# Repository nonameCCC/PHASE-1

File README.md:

# PHASE-1
A compact modularized audio DAC &amp; Headphone Amplifier.

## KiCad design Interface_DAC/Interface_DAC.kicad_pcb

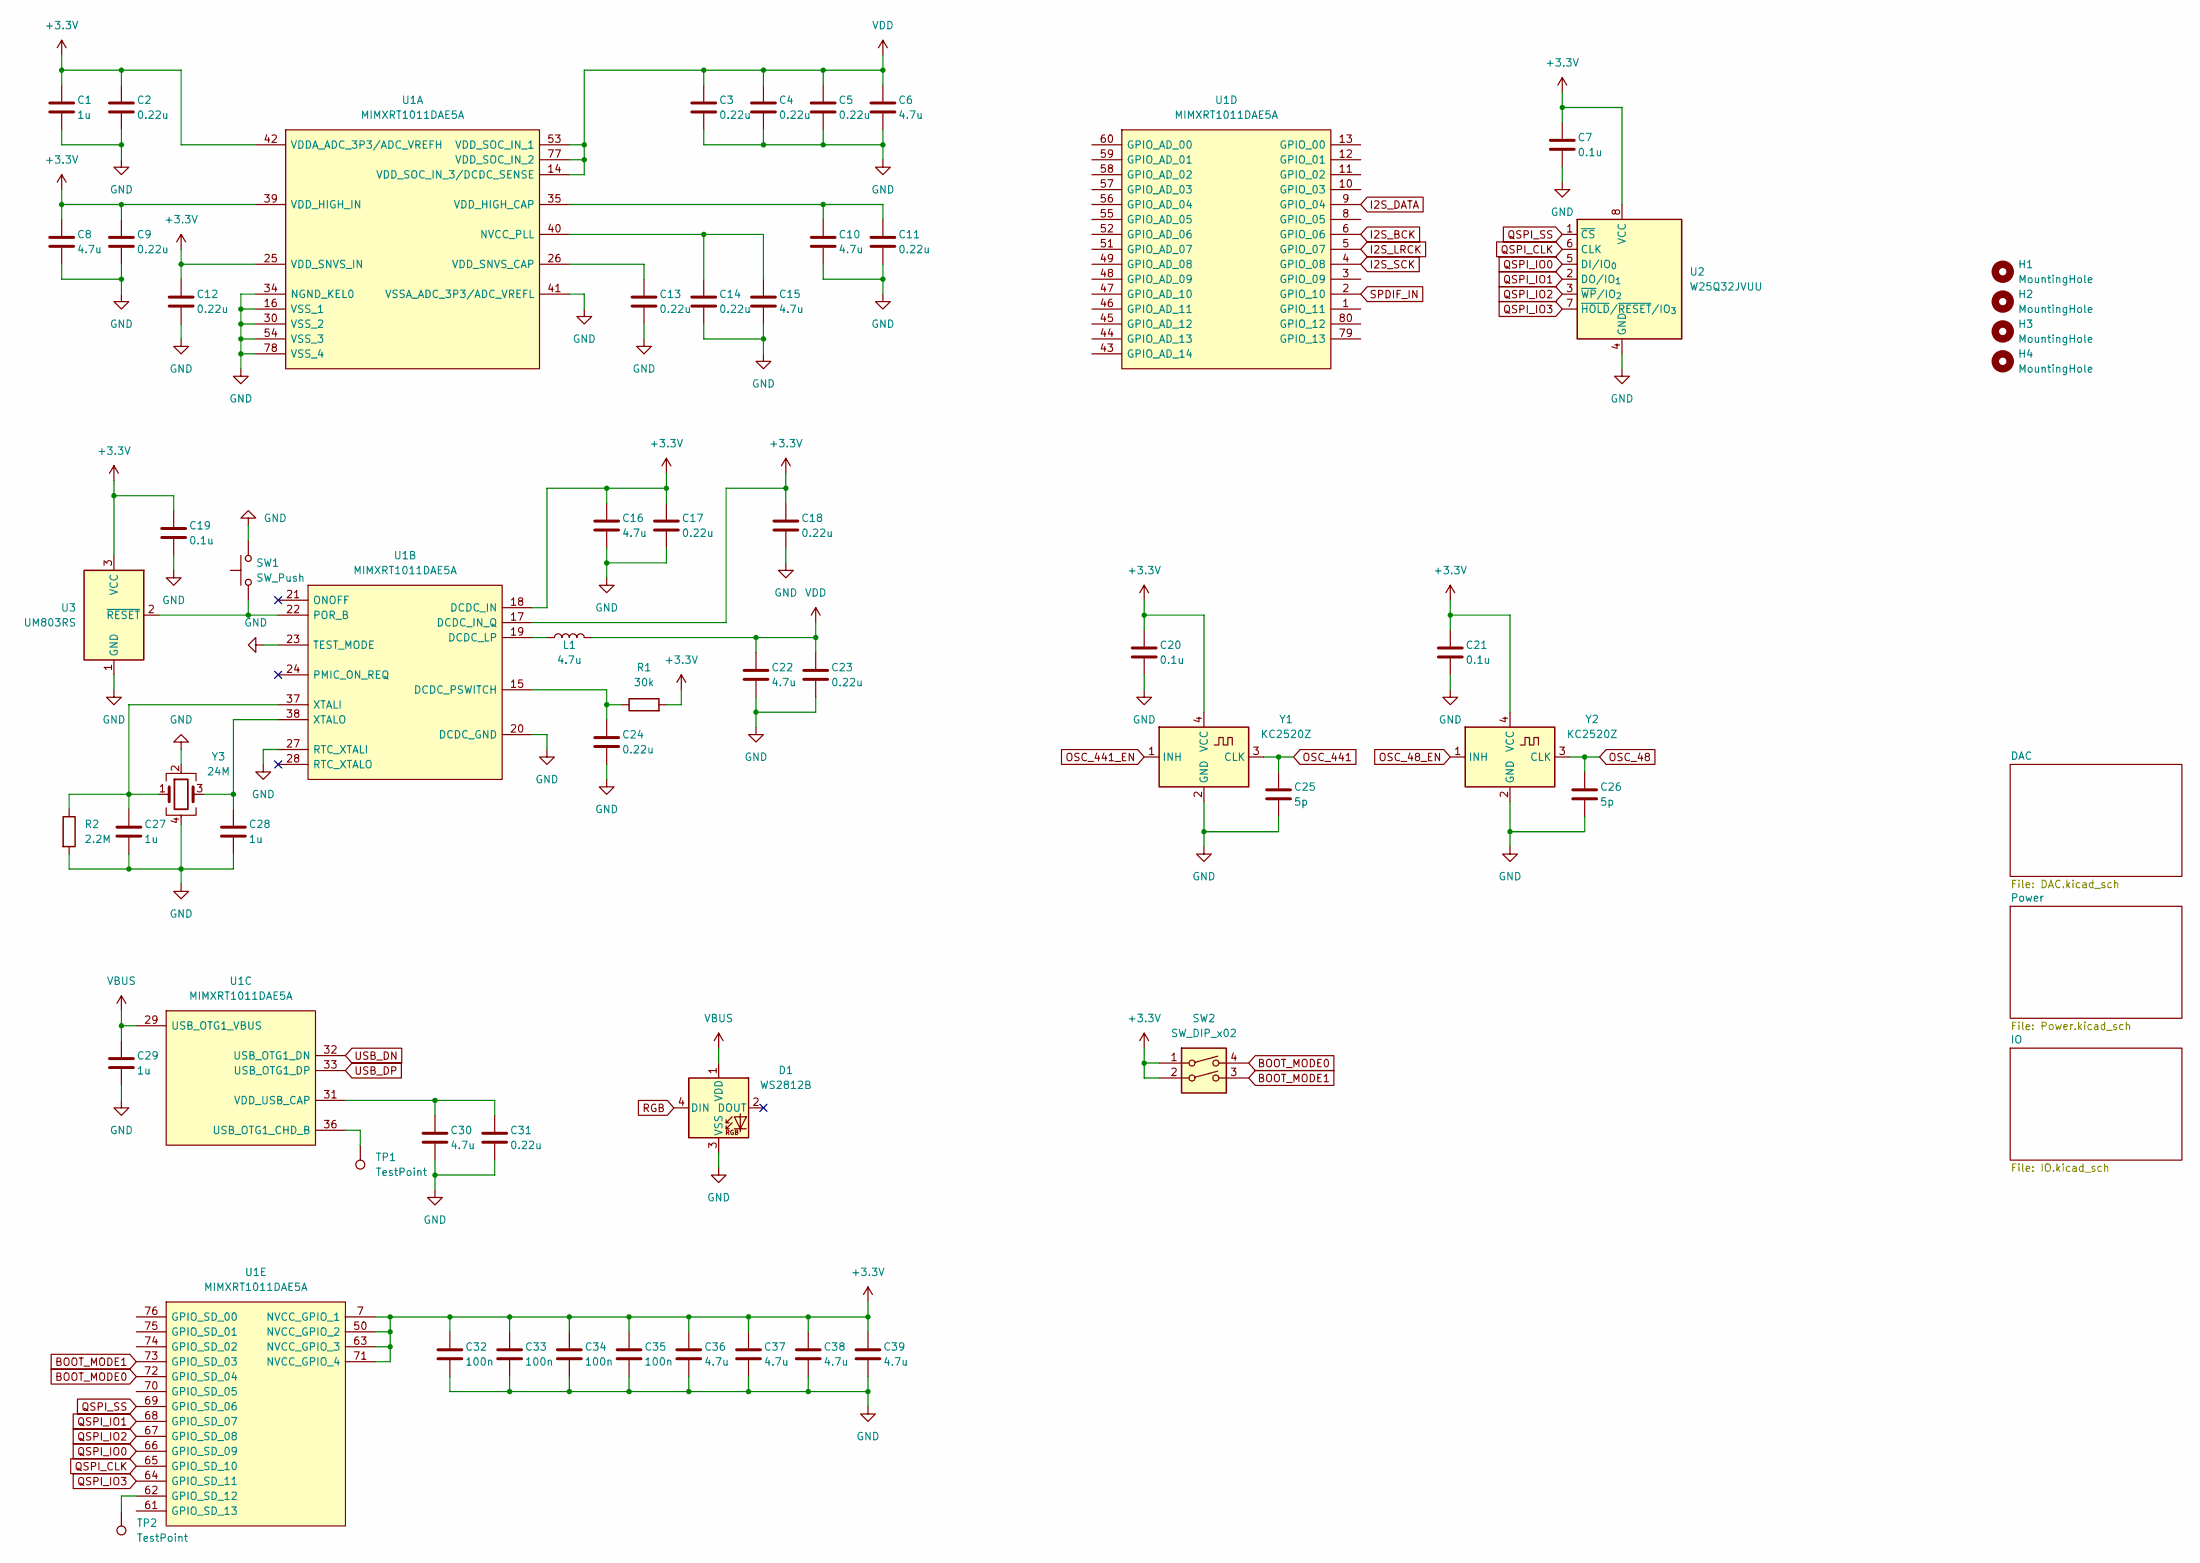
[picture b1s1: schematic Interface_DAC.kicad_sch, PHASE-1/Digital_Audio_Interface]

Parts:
C1, C27, C28, C29: 1u; C_0402_1005Metric
C2, C3, C4, C5, C9, C11, C12, C13, C14, C17, C18, C23, C24, C31: 0.22u; C_0402_1005Metric
C6, C8, C10, C15, C16, C22, C30, C36, C37, C38, C39: 4.7u; C_0402_1005Metric
C7, C19, C20, C21: 0.1u; C_0402_1005Metric
C25, C26: 5p; C_0402_1005Metric
C32, C33, C34, C35: 100n; C_0402_1005Metric
D1: WS2812B; 4020_WS2812
H1, H2, H3, H4: MountingHole; MountingHole_2.2mm_M2
L1: 4.7u; L_Murata_DFE201610P
R1: 30k; R_0402_1005Metric
R2: 2.2M; R_0402_1005Metric
SW1: SW_Push; PinHeader_1x02_P1.27mm_Vertical
SW2: SW_DIP_x02; SW_DIP_SPSTx02_Slide_Copal_CHS-02B_W7.62mm_P1.27mm
TP1, TP2: TestPoint; TestPoint_Pad_D1.0mm
U1: MIMXRT1011DAE5A; LQFP-80_12x12mm_P0.5mm; Manufacturer_Part_Number MIMXRT1011DAE5A; Mouser Part Number 771-MIMXRT1011DAE5A
U2: W25Q32JVUU; Winbond_USON-8-2EP_3x4mm_P0.8mm_EP0.2x0.8mm
U3: UM803RS; SOT-23
Y1, Y2: KC2520Z; Oscillator_SMD_Kyocera_KC2520Z-4Pin_2.5x2.0mm
Y3: 24M; Oscillator_SMD_Kyocera_KC2520Z-4Pin_2.5x2.0mm

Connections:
+3.3V: C1.1, C2.1, C7.1, C8.1, C9.1, C12.1, C16.1, C17.1, C18.1, C19.1, C20.1, C21.1, C32.1, C33.1, C34.1, C35.1, C36.1, C37.1, C38.1, C39.1, R1.2, SW2.1, SW2.2, U1.7 (NVCC_GPIO_1), U1.17 (DCDC_IN_Q), U1.18 (DCDC_IN), U1.25 (VDD_SNVS_IN), U1.39 (VDD_HIGH_IN), U1.42 (VDDA_ADC_3P3/ADC_VREFH), U1.50 (NVCC_GPIO_2), U1.63 (NVCC_GPIO_3), U1.71 (NVCC_GPIO_4), U2.8 (VCC), U3.3 (VCC), Y1.4 (VCC), Y2.4 (VCC); also elsewhere on the board
BOOT_MODE0: SW2.4, U1.72 (GPIO_SD_04)
BOOT_MODE1: SW2.3, U1.73 (GPIO_SD_03)
GND: C1.2, C2.2, C3.2, C4.2, C5.2, C6.2, C7.2, C8.2, C9.2, C10.2, C11.2, C12.2, C13.2, C14.2, C15.2, C16.2, C17.2, C18.2, C19.2, C20.2, C21.2, C22.2, C23.2, C24.2, C25.2, C26.2, C27.2, C28.2, C29.2, C30.2, C31.2, C32.2, C33.2, C34.2, C35.2, C36.2, C37.2, C38.2, C39.2, D1.3 (VSS), R2.2, SW1.2, U1.16 (VSS_1), U1.20 (DCDC_GND), U1.23 (TEST_MODE), U1.27 (RTC_XTALI), U1.30 (VSS_2), U1.34 (NGND_KEL0), U1.41 (VSSA_ADC_3P3/ADC_VREFL), U1.54 (VSS_3), U1.78 (VSS_4), U2.4 (GND), U3.1 (GND), Y1.2 (GND), Y2.2 (GND), Y3.2, Y3.4; also elsewhere on the board
I2S_BCK: U1.6 (GPIO_06); also elsewhere on the board
I2S_DATA: U1.9 (GPIO_04); also elsewhere on the board
I2S_LRCK: U1.5 (GPIO_07); also elsewhere on the board
I2S_SCK: U1.4 (GPIO_08); also elsewhere on the board
unnamed: C14.1, C15.1, U1.40 (NVCC_PLL)
unnamed: C10.1, C11.1, U1.35 (VDD_HIGH_CAP)
unnamed: C13.1, U1.26 (VDD_SNVS_CAP)
unnamed: L1.1, U1.19 (DCDC_LP)
unnamed: C24.1, R1.1, U1.15 (DCDC_PSWITCH)
unnamed: SW1.1, U1.22 (POR_B), U3.2 (~RESET)
unnamed: C27.1, R2.1, U1.37 (XTALI), Y3.1
unnamed: C28.1, U1.38 (XTALO), Y3.3
unnamed: TP1.1, U1.36 (USB_OTG1_CHD_B)
unnamed: C30.1, C31.1, U1.31 (VDD_USB_CAP)
unnamed: TP2.1, U1.62 (GPIO_SD_12)
OSC_48: C26.1, Y2.3 (CLK)
OSC_48_EN: Y2.1 (INH)
OSC_441: C25.1, Y1.3 (CLK)
OSC_441_EN: Y1.1 (INH)
QSPI_CLK: U1.65 (GPIO_SD_10), U2.6 (CLK)
QSPI_IO0: U1.66 (GPIO_SD_09), U2.5 (DI/IO_{0})
QSPI_IO1: U1.68 (GPIO_SD_07), U2.2 (DO/IO_{1})
QSPI_IO2: U1.67 (GPIO_SD_08), U2.3 (~WP/IO_{2})
QSPI_IO3: U1.64 (GPIO_SD_11), U2.7 (~HOLD/~RESET/IO_{3})
QSPI_SS: U1.69 (GPIO_SD_06), U2.1 (~CS)
RGB: D1.4 (DIN)
SPDIF_IN: U1.2 (GPIO_10)
USB_DN: U1.32 (USB_OTG1_DN); also elsewhere on the board
USB_DP: U1.33 (USB_OTG1_DP); also elsewhere on the board
VBUS: C29.1, D1.1 (VDD), U1.29 (USB_OTG1_VBUS); also elsewhere on the board
VDD: C3.1, C4.1, C5.1, C6.1, C22.1, C23.1, L1.2, U1.14 (VDD_SOC_IN_3/DCDC_SENSE), U1.53 (VDD_SOC_IN_1), U1.77 (VDD_SOC_IN_2)

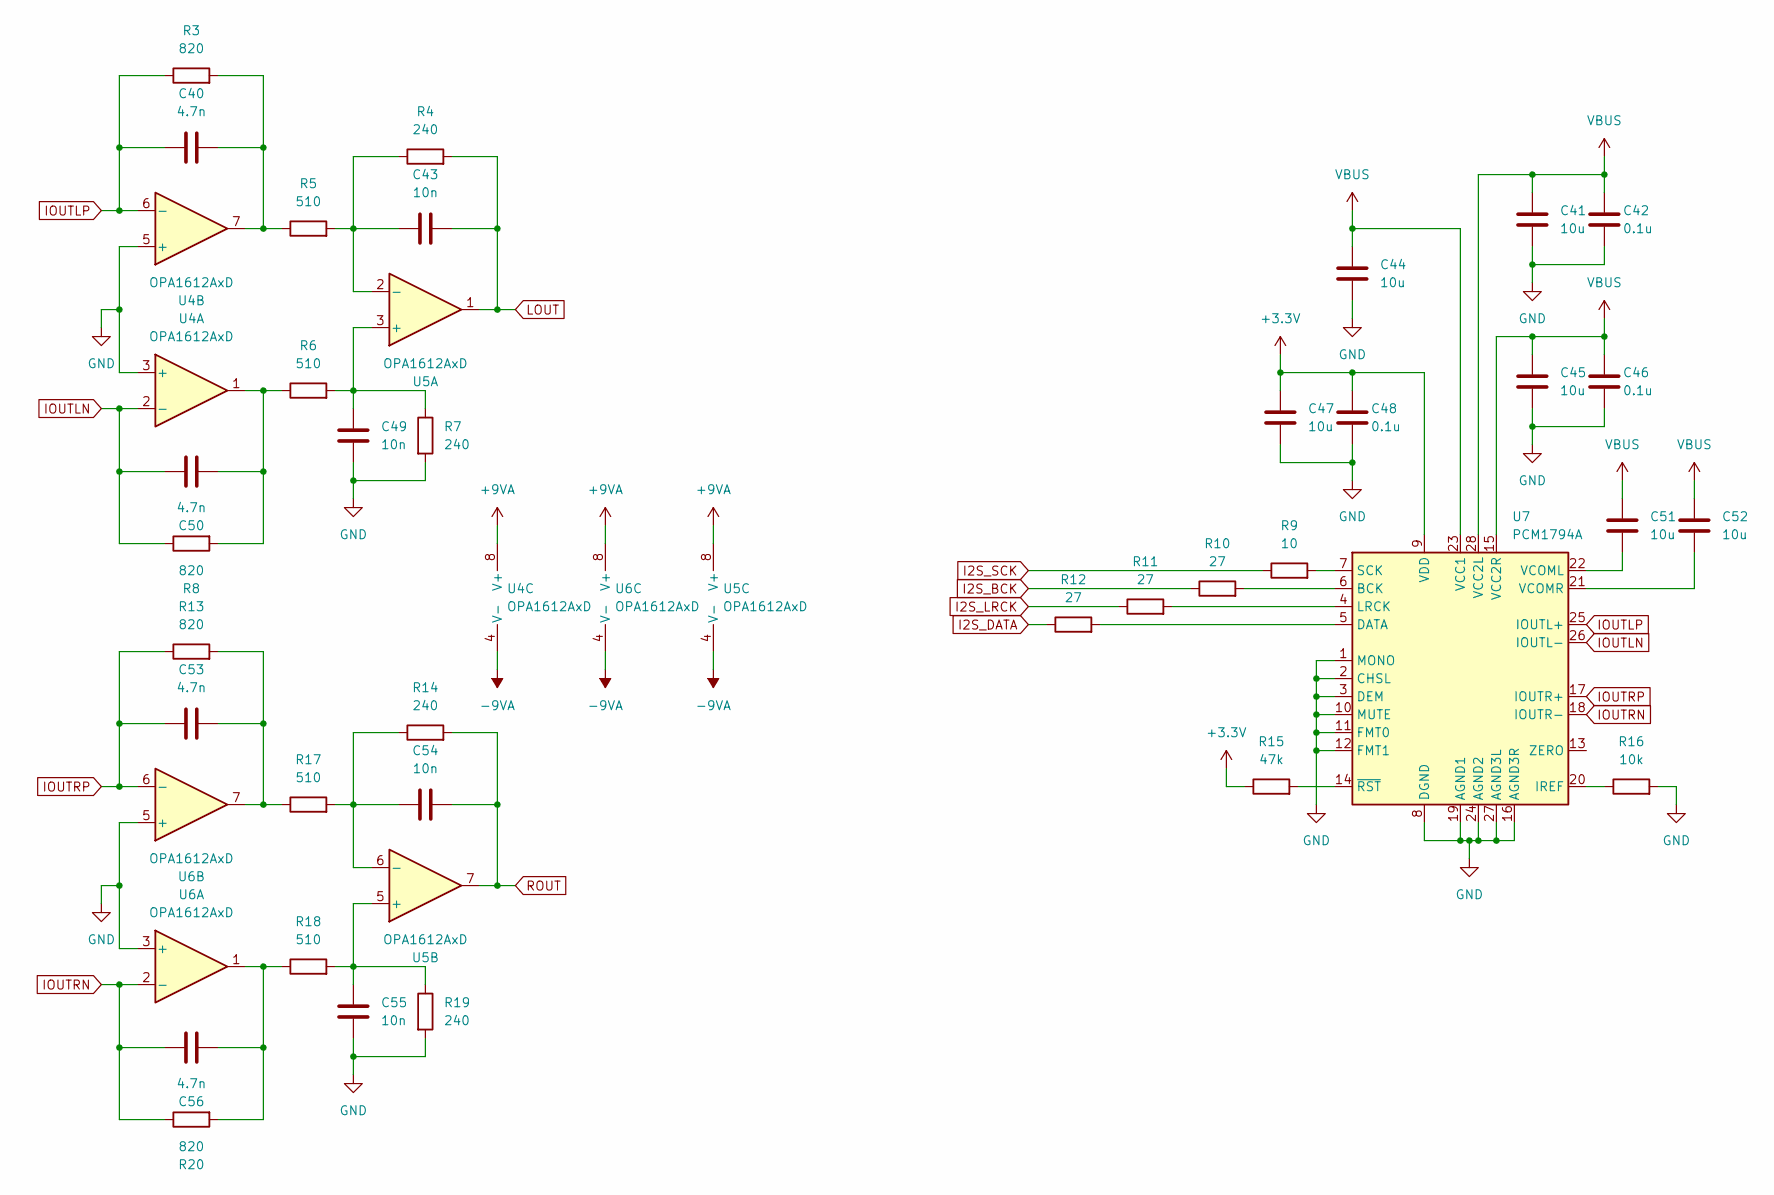
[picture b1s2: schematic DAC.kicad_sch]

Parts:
C40, C50, C53, C56: 4.7n; C_0402_1005Metric
C41, C44, C45, C47, C51, C52: 10u; C_0402_1005Metric
C42, C46, C48: 0.1u; C_0402_1005Metric
C43, C49, C54, C55: 10n; C_0402_1005Metric
R3, R8, R13, R20: 820; R_0402_1005Metric
R4, R7, R14, R19: 240; R_0402_1005Metric
R5, R6, R17, R18: 510; R_0402_1005Metric
R9: 10; R_0402_1005Metric
R10, R11, R12: 27; R_0402_1005Metric
R15: 47k; R_0402_1005Metric
R16: 10k; R_0402_1005Metric
U4, U6: OPA1612AxD; WSON-8-1EP_3x3mm_P0.5mm_EP1.2x2mm_ThermalVias
U5: OPA1612AxD; SOIC-8_3.9x4.9mm_P1.27mm
U7: PCM1794A; SSOP-28_5.3x10.2mm_P0.65mm

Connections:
+3.3V: C47.1, C48.1, R15.1, U7.9 (VDD); also elsewhere on the board
+9VA: U4.8 (V+), U5.8 (V+), U6.8 (V+); also elsewhere on the board
-9VA: U4.4 (V-), U5.4 (V-), U6.4 (V-); also elsewhere on the board
GND: C41.2, C42.2, C44.2, C45.2, C46.2, C47.2, C48.2, C49.2, C55.2, R7.2, R16.2, R19.2, U4.3 (+), U4.5 (+), U6.3 (+), U6.5 (+), U7.1 (MONO), U7.2 (CHSL), U7.3 (DEM), U7.8 (DGND), U7.10 (MUTE), U7.11 (FMT0), U7.12 (FMT1), U7.16 (AGND3R), U7.19 (AGND1), U7.24 (AGND2), U7.27 (AGND3L); also elsewhere on the board
I2S_BCK: R10.1; also elsewhere on the board
I2S_DATA: R12.1; also elsewhere on the board
I2S_LRCK: R11.1; also elsewhere on the board
I2S_SCK: R9.1; also elsewhere on the board
IOUTLN: C50.1, R8.1, U4.2 (-), U7.26 (IOUTL-)
IOUTLP: C40.1, R3.1, U4.6 (-), U7.25 (IOUTL+)
IOUTRN: C56.1, R20.1, U6.2 (-), U7.18 (IOUTR-)
IOUTRP: C53.1, R13.1, U6.6 (-), U7.17 (IOUTR+)
LOUT: C43.2, R4.2, U5.1
unnamed: C40.2, R3.2, R5.1, U4.7
unnamed: C50.2, R6.1, R8.2, U4.1
unnamed: C53.2, R13.2, R17.1, U6.7
unnamed: C56.2, R18.1, R20.2, U6.1
unnamed: C49.1, R6.2, R7.1, U5.3 (+)
unnamed: C43.1, R4.1, R5.2, U5.2 (-)
unnamed: C55.1, R18.2, R19.1, U5.5 (+)
unnamed: C54.1, R14.1, R17.2, U5.6 (-)
unnamed: R10.2, U7.6 (BCK)
unnamed: R12.2, U7.5 (DATA)
unnamed: R16.1, U7.20 (IREF)
unnamed: R11.2, U7.4 (LRCK)
unnamed: R9.2, U7.7 (SCK)
unnamed: C51.2, U7.22 (VCOML)
unnamed: C52.2, U7.21 (VCOMR)
unnamed: R15.2, U7.14 (~RST)
ROUT: C54.2, R14.2, U5.7
VBUS: C41.1, C42.1, C44.1, C45.1, C46.1, C51.1, C52.1, U7.15 (VCC2R), U7.23 (VCC1), U7.28 (VCC2L); also elsewhere on the board

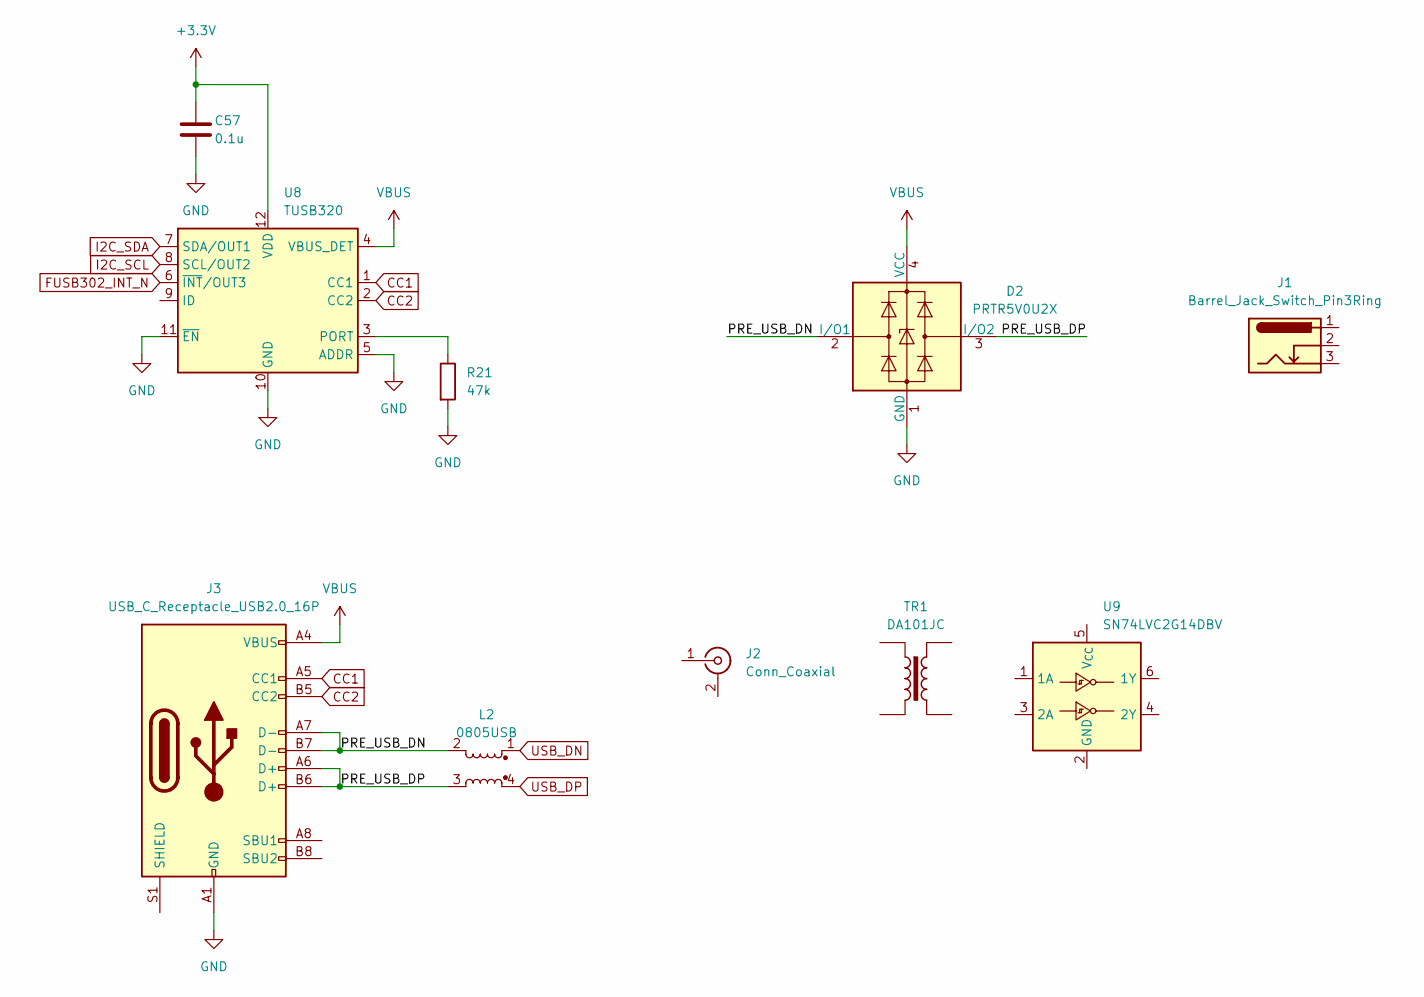
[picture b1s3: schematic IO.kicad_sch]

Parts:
C57: 0.1u; C_0402_1005Metric
D2: PRTR5V0U2X; SOT-143
J1: Barrel_Jack_Switch_Pin3Ring; DC044
J2: Conn_Coaxial; PJRAN1X1U04
J3: USB_C_Receptacle_USB2.0_16P; USB_C_Receptacle_GCT_USB4110
L2: 0805USB; L_CommonModeChoke_Coilcraft_0805USB
R21: 47k; R_0402_1005Metric
TR1: DA101JC
U8: TUSB320; Texas_X2QFN-12_1.6x1.6mm_P0.4mm
U9: SN74LVC2G14DBV; SOT-23-6

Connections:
+3.3V: C57.1, U8.12 (VDD); also elsewhere on the board
/IO/PRE_USB_DN: D2.2 (I/O1), J3.A7 (D-), J3.B7 (D-), L2.2
/IO/PRE_USB_DP: D2.3 (I/O2), J3.A6 (D+), J3.B6 (D+), L2.3
CC1: J3.A5 (CC1), U8.1 (CC1)
CC2: J3.B5 (CC2), U8.2 (CC2)
FUSB302_INT_N: U8.6 (~INT/OUT3)
GND: C57.2, D2.1 (GND), J3.A1 (GND), J3.A12 (GND), J3.B1 (GND), J3.B12 (GND), R21.2, U8.5 (ADDR), U8.10 (GND), U8.11 (~EN); also elsewhere on the board
I2C_SCL: U8.8 (SCL/OUT2)
I2C_SDA: U8.7 (SDA/OUT1)
unnamed: R21.1, U8.3 (PORT)
USB_DN: L2.1; also elsewhere on the board
USB_DP: L2.4; also elsewhere on the board
VBUS: D2.4 (VCC), J3.A4 (VBUS), J3.A9 (VBUS), J3.B4 (VBUS), J3.B9 (VBUS), U8.4 (VBUS_DET); also elsewhere on the board

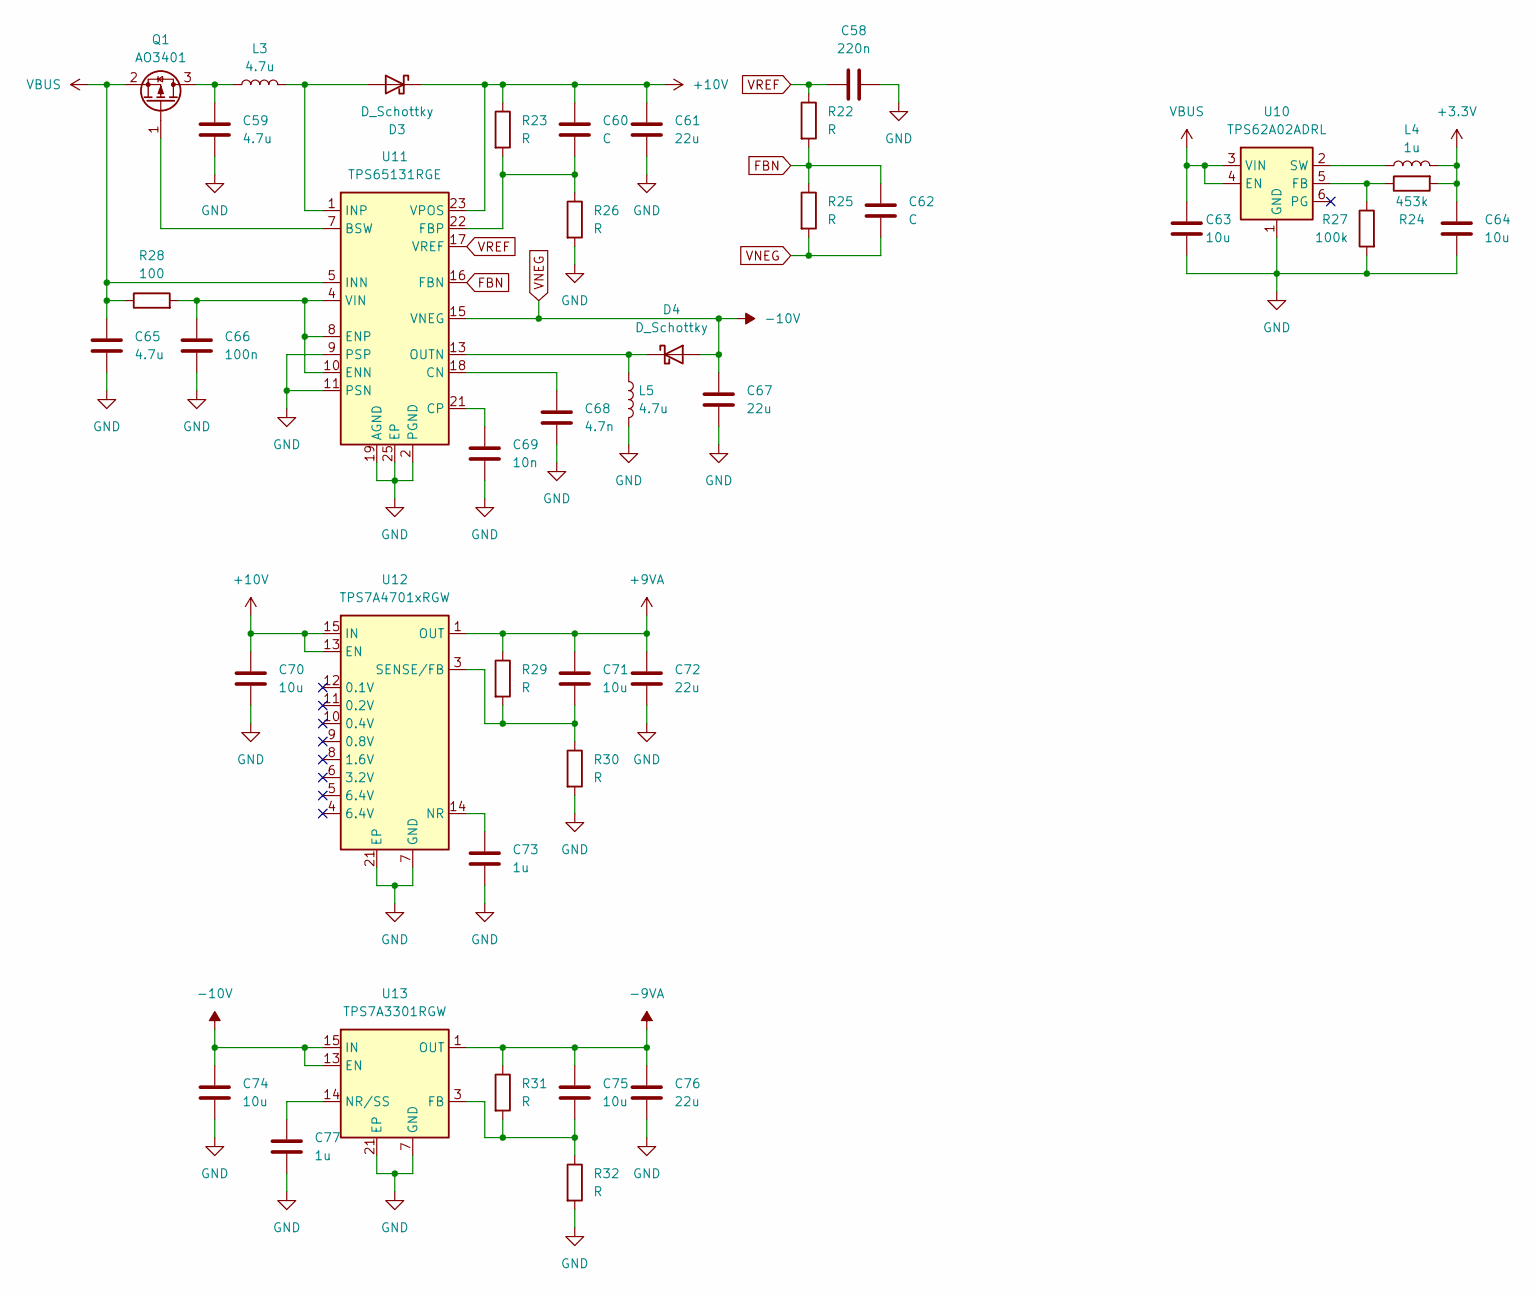
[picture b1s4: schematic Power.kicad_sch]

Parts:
C58: 220n; C_0402_1005Metric
C59, C65: 4.7u; C_0402_1005Metric
C60, C62: C; C_0402_1005Metric
C61, C67, C72, C76: 22u; C_0603_1608Metric
C63, C64, C70, C71, C74, C75: 10u; C_0402_1005Metric
C66: 100n; C_0402_1005Metric
C68: 4.7n; C_0402_1005Metric
C69: 10n; C_0402_1005Metric
C73, C77: 1u; C_0402_1005Metric
D3, D4: D_Schottky; D_SOD-323
L3, L5: 4.7u; L_Murata_DFE201610P
L4: 1u; L_Murata_DFE201610P
Q1: AO3401; SOT-23
R22, R23, R25, R26, R29, R30, R31, R32: R; R_0402_1005Metric
R24: 453k; R_0402_1005Metric
R27: 100k; R_0402_1005Metric
R28: 100; R_0402_1005Metric
U10: TPS62A02ADRL; SOT-563
U11: TPS65131RGE; VQFN-24-1EP_4x4mm_P0.5mm_EP2.45x2.45mm_ThermalVias
U12: TPS7A4701xRGW; Texas_RGW0020A_VQFN-20-1EP_5x5mm_P0.65mm_EP3.15x3.15mm_Ther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
U13: TPS7A3301RGW; Texas_RGW0020A_VQFN-20-1EP_5x5mm_P0.65mm_EP3.15x3.15mm_Ther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

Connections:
+3.3V: C64.1, L4.2, R24.2; also elsewhere on the board
+9VA: C71.1, C72.1, R29.1, U12.1 (OUT), U12.20 (OUT); also elsewhere on the board
+10V: C60.1, C61.1, C70.1, D3.1 (K), R23.1, U11.23 (VPOS), U12.13 (EN), U12.15 (IN), U12.16 (IN)
-9VA: C75.1, C76.1, R31.1, U13.1 (OUT), U13.20 (OUT); also elsewhere on the board
FBN: C62.1, R22.2, R25.1, U11.16 (FBN)
GND: C58.2, C59.2, C61.2, C63.2, C64.2, C65.2, C66.2, C67.2, C68.2, C69.2, C70.2, C72.2, C73.2, C74.2, C76.2, C77.2, L5.2, R26.2, R27.2, R30.2, R32.2, U10.1 (GND), U11.2 (PGND), U11.3 (PGND), U11.9 (PSP), U11.11 (PSN), U11.19 (AGND), U11.25 (EP), U12.7 (GND), U12.21 (EP), U13.7 (GND), U13.21 (EP); also elsewhere on the board
unnamed: D3.2 (A), L3.2, U11.1 (INP), U11.24 (INP)
unnamed: D4.1 (K), L5.1, U11.13 (OUTN), U11.14 (OUTN)
unnamed: C59.1, L3.1, Q1.3 (D)
unnamed: Q1.1 (G), U11.7 (BSW)
unnamed: R24.1, R27.1, U10.5 (FB)
unnamed: L4.1, U10.2 (SW)
unnamed: C68.1, U11.18 (CN)
unnamed: C69.1, U11.21 (CP)
unnamed: C66.1, R28.2, U11.4 (VIN), U11.8 (ENP), U11.10 (ENN)
unnamed: C60.2, R23.2, R26.1, U11.22 (FBP)
unnamed: C73.1, U12.14 (NR)
unnamed: C71.2, R29.2, R30.1, U12.3 (SENSE/FB)
unnamed: C75.2, R31.2, R32.1, U13.3 (FB)
unnamed: C77.1, U13.14 (NR/SS)
VBUS: C63.1, C65.1, Q1.2 (S), R28.1, U10.3 (VIN), U10.4 (EN), U11.5 (INN), U11.6 (INN); also elsewhere on the board
VNEG: C62.2, C67.1, C74.1, D4.2 (A), R25.2, U11.15 (VNEG), U13.13 (EN), U13.15 (IN), U13.16 (IN)
VREF: C58.1, R22.1, U11.17 (VREF)

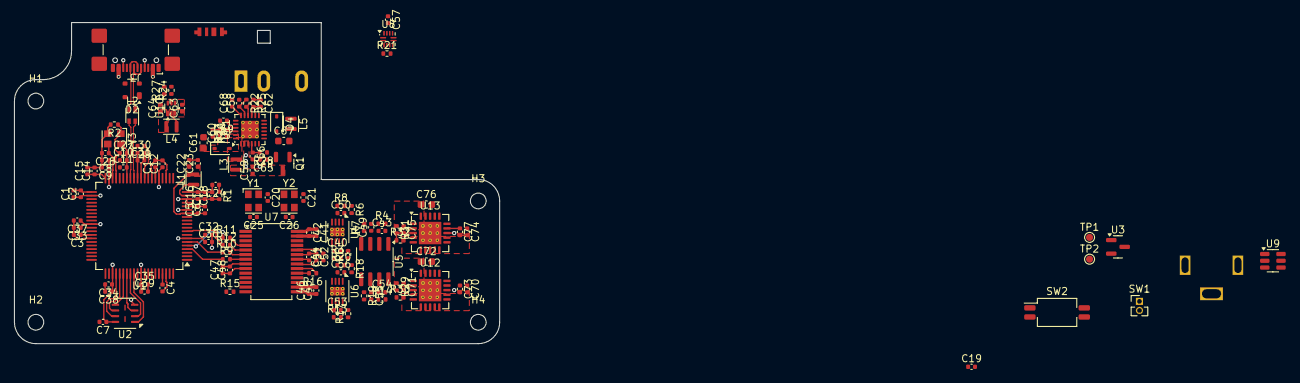
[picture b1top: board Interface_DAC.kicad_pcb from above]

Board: 4 copper layers, 68.0 x 45.0 mm, 146 parts (0 on the bottom side), 78 nets.

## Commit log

2025-11-06 Create KiCad Project for the Digital Interface
2025-11-08 Modified the Symbol of MIMXRT1011DAE5A
2025-11-09 Finished the Design of Peripheral Circuit
2025-11-09 Finished Circuit Design of External Flash, Power Supply, etc.
2025-11-10 Peripheral Circuit Design Improvement
2025-11-10 Added Amplifier Module and Its Power Supply Design
2025-11-11 Simplified Power Supply, Modified POR Circuit and Added DIP Switch for Boot Mode Select
2025-11-26 Detail Improvement
2025-11-26 Added Footprints for DC Barrel Jack and RCA Coaxial Jack
2025-12-03 Rename Project and Its Folder
2025-12-05 Create New Project and Rename Existing Project
2025-12-05 Revert "Create New Project and Rename Existing Project"
    This reverts commit 3b9dd97898193b6fd56ddcb8e4aa39248ad02a2e.
2025-12-08 Major Update
    Added footprint for RGB LED
    Updated DAC circuit design
    Updated FUSB302B circuit connection
    Rearranged schematic for DAC and IO
2025-12-08 Footprint Arrangement
2025-12-11 Schematic Tinkering and PCB Layout
2025-12-22 Microcontroller Swap
    Changed the microcontroller from NXP MIMXRT1011DAE5A to ST STM32F446RET6
2025-12-23 Schematic Design and Library Relink
2025-12-23 Create Symbol for USB3320-EZK
2025-12-23 Revert "Create Symbol for USB3320-EZK"
    This reverts commit 0f8501c4fbb28d617c720a0b53a767fac1f4d862.
2025-12-23 Schematic Design
